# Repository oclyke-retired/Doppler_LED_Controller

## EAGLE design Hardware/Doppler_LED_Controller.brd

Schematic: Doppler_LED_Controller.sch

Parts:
C1, C3, C4, C6, C12, C13, C14, C15, C16, C20: 0.1uF; 0603
C2, C10, C11, C17, C18: 2.2uF; 0603
C5, C9: 10uF; 0603
C7, C8: 18pF; 0603
D1: ESPTX-GREEN; LED-0603
D2: ESP_STAT; APA102_2020_LONG
D3: ESPRX-YELLOW; LED-0603
D4: ULED1-BLUE; LED-0603
D5: ULED2-WHITE; LED-0603
D6: U7TX-GREEN; LED-0603
D8: U7RX-YELLOW; LED-0603
D10: 5.6V; SOD-323
D11: 3A/10V/280mV; SOD-323
D12: PWR-RED; LED-0603
F1: PPTC_6V500MA; 0805
FD1, FD2, FD3, FD4: FIDUCIAL1X2; FIDUCIAL-1X2
H1, H2, H3, H4: STAND-OFF
J1, J2: USB_MICRO-B_HALF_PTH_MILL; USB-MICROB-PTH-MILL
J3: CORTEX_DEBUG_PTH; 2X5-PTH-1.27MM
JP1: ALED1_VOUT_SEL; SMT-JUMPER_3_1-NC_TRACE_SILK
JP2: ALED2_VOUT_SEL; SMT-JUMPER_3_1-NC_TRACE_SILK
JP3: ALED3_VOUT_SEL; SMT-JUMPER_3_1-NC_TRACE_SILK
JP4: ALED4_VOUT_SEL; SMT-JUMPER_3_1-NC_TRACE_SILK
JP5, JP7: I2C1_VOUT_SEL; SMT-JUMPER_3_1-NC_TRACE_SILK
JP6: JUMPER-SMT_2_NO_SILK; SMT-JUMPER_2_NO_SILK
JP9: IMU_VSEL; SMT-JUMPER_3_1-NC_TRACE_SILK
JP10: MPU9250; SMT-JUMPER_2_NO_SILK
JP11: DEFUSE; SMT-JUMPER_2_NO_SILK
M1: EXT_SWTCH; 1X03_SMD_0.1IN
M2: EXT_SWTCH; 3_PIN_LOCK
M3: ALED1_LOCK; 3_PIN_LOCK
M4: ALED2_LOCK; 3_PIN_LOCK
M5: ALED3_LOCK; 3_PIN_LOCK
M6: ALED4_LOCK; 3_PIN_LOCK
M7: ALED1_SMD; 1X03_SMD_0.1IN
M8: ALED2_SMD; 1X03_SMD_0.1IN
M9: ALED3_SMD; 1X03_SMD_0.1IN
M10: ALED4_SMD; 1X03_SMD_0.1IN
M11: I2C1_LOCK; 4_PIN_LOCK
M13: U7_LOCK; 4_PIN_LOCK
M15: I2C1_SMD; 1X04_SMD_0.1IN
M17: U7_SMD; 1X04_SMD_0.1IN
M19: SIG_IN_LOCK; 4_PIN_LOCK
M20: SIG_IN_SMD; 1X04_SMD_0.1IN
M21: SD; SD_AMPHENOL_PUSH_PULL
M22: CONN_SMD_2; 1X02_SMD_0.1IN
M23: CONN_LOCK_2-5055670271; 2_PIN_LOCK
Q1: TRANS_NPN_DUAL-MBT3904DW1T1; SC70-6
Q2, Q3, Q4, Q5, Q6, Q7, Q8, Q9, Q10, Q12, Q14, Q16, Q18, Q19, Q20, Q21: AMP_MOSFET_NCH-2N7002K; SOT23-3
Q22, Q23: 4.3A/20V/54mΩ; SOT23-3
R1, R10: DNP; 0603
R3, R4, R6, R9, R16, R17, R18, R19, R20, R21, R22, R23, R24, R25, R26, R27, R28, R29, R30, R31, R32, R33, R34, R35, R36, R38, R39, R43, R47, R51, R57, R58, R59, R60, R61, R62, R63, R64, R65, R66, R67, R68: 10k; 0603
R7, R8, R11, R12, R53, R55, R69: 1k; 0603
R13, R14: 20; 0603
R37, R41, R45, R49: 2.2k; 0603
S1, S2, S3: US2; TACTILE_SWITCH_SMD_5.2MM
S4: STM_!RST; TACTILE_SWITCH_SMD_5.2MM
S5: US1; TACTILE_SWITCH_SMD_5.2MM
TP1: EDRDY; PAD.03X.04
TP3: ERX0; PAD.03X.04
TP4: ETX0; PAD.03X.04
TP5: E!RTS; PAD.03X.04
TP6: E!DTR; PAD.03X.04
TP7: EMOSI; PAD.03X.04
TP8: EMISO; PAD.03X.04
TP9: ESCLK; PAD.03X.04
TP10: ECS; PAD.03X.04
TP11: ESSI; PAD.03X.04
TP12: ESSCK; PAD.03X.04
TP13: E!RST; PAD.03X.04
TP17: VDDIO; PAD.03X.04
TP18: 1V8; PAD.03X.04
TP20: S1Si; PAD.03X.04
TP21: S1SO; PAD.03X.04
TP22: S1SCLk; PAD.03X.04
TP23: CSSD; PAD.03X.04
TP24: CSIMU; PAD.03X.04
TP25: SDCD; PAD.03X.04
TP29: CSIMUIO; PAD.03X.04
TP30: IMUINT; PAD.03X.04
TP31: IMUFS; PAD.03X.04
TP34: AL1D; PAD.03X.04
TP35: AL2D; PAD.03X.04
TP36: AL3D; PAD.03X.04
TP37: AL4D; PAD.03X.04
TP38: AL1V; PAD.03X.04
TP39: AL2V; PAD.03X.04
TP40: AL3V; PAD.03X.04
TP41: AL4V; PAD.03X.04
TP42: AL1C; PAD.03X.04
TP43: AL2C; PAD.03X.04
TP44: AL3C; PAD.03X.04
TP45: AL4C; PAD.03X.04
TP47: VRPP; PAD.03X.04
TP48: VOVP; PAD.03X.04
TP49: VUSB; PAD.03X.04
TP50: 5V; PAD.03X.04
TP51: 3V3; PAD.03X.04
TP52: GND; PAD.03X.04
TP53: IIC1SDA; PAD.03X.04
TP54: IIC1SCL; PAD.03X.04
TP57: U7TX; PAD.03X.04
TP58: U7RX; PAD.03X.04
TP62: STMR; PAD.03X.04
TP68: SWCLK; PAD.03X.04
TP69: BRK; PAD.03X.04
TP70: LTS; PAD.03X.04
TP71: RTS; PAD.03X.04
TP72: REV; PAD.03X.04
TP78: SWDIO; PAD.03X.04
U1: ESP-WROOM-32
U3: STM32F765VTG6; LQFP-100
U4: 1.8V; DDC5
U5: 9DoF IMU; QFN24-3X3
U6: TXB0108DQSR; UFDFN-20
U7: 3.3V; SOT23-5
U8: CH340C; SO016
U9: W25Q32FVSS; SOIC-8
U$98: REV_NUM
Y1: 24MHz; CRYSTAL-SMD-5X3.2-4PAD

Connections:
1.8V: JP9.3, TP18.P$1, U4.5 (VOUT)
3.3V: C2.1, C3.1, C4.1, C5.1, C6.1, C9.1, C14.1, C16.1, C18.1, C20.1, D1.A, D2.4VCC, D3.A, D4.A, D5.A, D6.A, D8.A, D12.A, J3.1 (VCC), JP1.1, JP2.1, JP3.1, JP4.1, JP5.3, JP6.1, JP7.3, JP9.1, M1.P$2 (2), M2.P$2 (2), M21.CD_SW2, M21.P$4 (VDD), Q2.1 (G), Q3.1 (G), Q4.1 (G), Q5.1 (G), Q6.1 (G), Q7.1 (G), Q8.1 (G), Q9.1 (G), Q10.1 (G), Q12.1 (G), Q14.1 (G), Q16.1 (G), Q18.1 (G), Q19.1 (G), Q20.1 (G), Q21.1 (G), R6.2, R9.2, R17.2, R18.2, R19.2, R21.2, R22.2, R23.2, R24.2, R29.2, R30.2, R31.2, R32.2, R37.2, R39.2, R45.2, R47.2, R57.2, R58.2, R59.2, R60.2, R65.2, R67.2, S3.3 (2), S3.4 (2), S5.3 (2), S5.4 (2), TP51.P$1, U1.2 (3V3), U3.P$6 (6.VBAT), U3.P$11 (11.VDD), U3.P$20 (20.VREF), U3.P$21 (21.VDDA), U3.P$27 (27.VDD), U3.P$50 (50.VDD), U3.P$75 (75.VDD), U3.P$100 (100.VDD), U4.1 (VIN), U4.3 (EN), U5.13 (VDD), U6.16 (VCCB), U7.5 (OUT), U8.4 (V3), U8.16 (VCC), U9.8 (VCC)
5V: C17.1, D11.C, JP1.3, JP2.3, JP3.3, JP4.3, JP5.1, JP7.1, Q23.2 (S), TP50.P$1, U7.1 (IN), U7.3 (EN)
ALED1_MOSI_VOUT: M3.P$1 (1), M7.P$1 (1), Q6.3 (D), R33.1
ALED1_SCLK_VOUT: M3.P$3 (3), M7.P$3 (3), Q2.3 (D), R25.1
ALED1_VOUT: JP1.2, R25.2, R33.2, TP38.P$1
ALED2_MOSI_VOUT: M4.P$1 (1), M8.P$1 (1), Q7.3 (D), R34.1
ALED2_SCLK_VOUT: M4.P$3 (3), M8.P$3 (3), Q3.3 (D), R26.1
ALED2_VOUT: JP2.2, R26.2, R34.2, TP39.P$1
ALED3_MOSI_VOUT: M5.P$1 (1), M9.P$1 (1), Q8.3 (D), R35.1
ALED3_SCLK_VOUT: M5.P$3 (3), M9.P$3 (3), Q4.3 (D), R27.1
ALED3_VOUT: JP3.2, R27.2, R35.2, TP40.P$1
ALED4_MOSI_VOUT: M6.P$1 (1), M10.P$1 (1), Q9.3 (D), R36.1
ALED4_SCLK_VOUT: M6.P$3 (3), M10.P$3 (3), Q5.3 (D), R28.1
ALED4_VOUT: JP4.2, R28.2, R36.2, TP41.P$1
BOOT0: JP6.2, R38.2, U3.P$94 (94.BOOT0)
BRK: Q18.2 (S), R57.1, TP69.P$1, U3.P$81 (81.PD0)
BRK_12V: M19.P$1 (1), M20.P$1 (1), Q18.3 (D), R61.1
CS_ESP: TP10.P$1, U1.29 (CS0_V/IO5), U3.P$4 (4.PE5)
CS_IMU: R67.1, TP24.P$1, U3.P$3 (3.PE4), U6.20 (B1)
CS_IMU_VDDIO: TP29.P$1, U5.22 (!CS), U6.1 (A1)
CS_SD: M21.P$2 (CD/DAT3), R65.1, TP23.P$1, U3.P$2 (2.PE3)
ESP_0: Q1.1 (E), R6.1, S1.1, S1.2 (1), U1.25 (IO0)
ESP_!DTR: Q1.6 (C), R3.2, TP6.P$1, U8.13 (!DTR)
ESP_!RESET: C1.1, Q1.3 (C), R9.1, S2.1, S2.2 (1), TP13.P$1, U1.3 (EN)
ESP_!RTS: Q1.4 (E), R4.2, TP5.P$1, U8.14 (!RTS)
ESP_DRDY: TP1.P$1, U1.24 (IO2), U3.P$9 (9.PC15)
ESP_RXI0: R8.1, TP3.P$1, U1.34 (RXD), U8.2 (TXO)
ESP_STAT_MOSI: D2.1DIN, TP11.P$1, U1.16 (MOSI_H/IO13)
ESP_STAT_SCLK: D2.2CIN, TP12.P$1, U1.13 (SCK_H/IO14)
ESP_TXO0: R7.1, TP4.P$1, U1.35 (TXD), U8.3 (RXI)
ESP_USB_DM: J1.D-, U8.6 (UD-)
ESP_USB_DP: J1.D+, U8.5 (UD+)
GND: C1.2, C2.2, C3.2, C4.2, C5.2, C6.2, C7.1, C8.1, C9.2, C10.2, C11.2, C12.1, C13.2, C14.2, C15.2, C16.2, C17.2, C18.2, C20.2, D2.3GND, D10.A, J1.GND, J2.GND, J3.3 (GND), J3.5 (GND), J3.9 (GNDDTCT), M3.P$2 (2), M4.P$2 (2), M5.P$2 (2), M6.P$2 (2), M7.P$2 (2), M8.P$2 (2), M9.P$2 (2), M10.P$2 (2), M11.P$4 (4), M13.P$4 (4), M15.P$4 (4), M17.P$4 (4), M21.P$6 (VSS1), M22.P$1 (1), M23.P$2 (1), Q22.1 (G), R1.1, R10.1, R16.1, R20.1, R38.1, R61.2, R62.2, R63.2, R64.2, R66.1, R68.1, R69.1, S1.3 (2), S1.4 (2), S2.3 (2), S2.4 (2), S4.3 (2), S4.4 (2), TP52.P$1, U1.1 (GND), U1.15 (GND), U1.38 (GND), U1.GND, U3.P$10 (10.VSS), U3.P$19 (19.VSSA), U3.P$26 (26.VSS), U3.P$49 (49.VSS), U3.P$74 (74.VSS), U3.P$99 (99.VSS), U4.2 (GND), U4.4 (GND), U5.18 (GND), U5.20 (RESV20), U6.15 (GND), U7.2 (GND), U8.1 (GND), U9.4 (GND), Y1.2 (GND), Y1.4 (GND)
I2C1_SCL: Q10.2 (S), R37.1, TP54.P$1, U3.P$95 (95.PB8)
I2C1_SCL_VOUT: M11.P$1 (1), M15.P$1 (1), Q10.3 (D), R41.1
I2C1_SDA: Q14.2 (S), R45.1, TP53.P$1, U3.P$93 (93.PB7)
I2C1_SDA_VOUT: M11.P$2 (2), M15.P$2 (2), Q14.3 (D), R49.1
I2C1_VOUT: JP5.2, M11.P$3 (3), M15.P$3 (3), R41.2, R49.2
I2C2_SCL: U3.P$46 (46.PB10)
I2C2_SDA: U3.P$47 (47.PB11)
IMU_FSYNC: TP31.P$1, U3.P$64 (64.PC7), U6.12 (B7)
IMU_FSYNC_VDDIO: U5.11 (FSYNC), U6.9 (A7)
IMU_INT: TP30.P$1, U3.P$63 (63.PC6), U6.11 (B8)
IMU_INT_VDDIO: U5.12 (INT), U6.10 (A8)
IMU_RESV1: JP10.1, U5.1 (RESV1)
IMU_VDDIO: C13.1, JP9.2, JP10.2, TP17.P$1, U5.8 (VDDIO), U6.5 (VCCA), U6.6 (OE)
LTS: Q19.2 (S), R58.1, TP70.P$1, U3.P$82 (82.PD1)
LTS_12V: M19.P$2 (2), M20.P$2 (2), Q19.3 (D), R62.1
unnamed: J2.SHIELD, J2.SHIELD2 (SHIELD), J2.SHIELD3 (SHIELD), J2.SHIELD4 (SHIELD), J2.SHIELD5 (SHIELD), J2.SHIELD6 (SHIELD), J2.SHIELD7 (SHIELD), J2.SHIELD8 (SHIELD), J2.SHIELD9 (SHIELD), J2.SHIELD10 (SHIELD), R10.2
unnamed: C11.1, U3.P$73 (73.VCAP2)
unnamed: J1.SHIELD, J1.SHIELD2 (SHIELD), J1.SHIELD3 (SHIELD), J1.SHIELD4 (SHIELD), J1.SHIELD5 (SHIELD), J1.SHIELD6 (SHIELD), J1.SHIELD7 (SHIELD), J1.SHIELD8 (SHIELD), J1.SHIELD9 (SHIELD), J1.SHIELD10 (SHIELD), R1.2
unnamed: C10.1, U3.P$48 (48.VCAP1)
unnamed: Q1.5 (B), R3.1
unnamed: Q1.2 (B), R4.1
unnamed: C15.1, U5.10 (REGOUT)
unnamed: D8.C, R55.2
unnamed: J3.2 (SWDIO/TMS), R13.1
unnamed: J3.4 (SWDCLK/TCK), R14.1
unnamed: D6.C, R53.2
unnamed: D1.C, R7.2
unnamed: D3.C, R8.2
unnamed: D12.C, R69.2
unnamed: D5.C, R12.2
unnamed: D4.C, R11.2
PH0: C7.2, U3.P$12 (12.PH0), Y1.3 (2)
PH1: C8.2, U3.P$13 (13.PH1), Y1.1
QSPI_BK1_IO0: Q9.2 (S), R32.1, TP37.P$1, U3.P$58 (58.PD11)
QSPI_BK1_IO1: U3.P$59 (59.PD12)
QSPI_BK1_IO2: U3.P$1 (1.PE2)
QSPI_BK1_IO3: U3.P$60 (60.PD13)
QSPI_BK1_NCS: U3.P$92 (92.PB6)
QSPI_BK2_IO0: U3.P$37 (37.PE7), U9.5 (SI(D0))
QSPI_BK2_IO1: U3.P$38 (38.PE8), U9.2 (SO(D1))
QSPI_BK2_IO2: U3.P$39 (39.PE9), U9.3 (!WP!(D2))
QSPI_BK2_IO3: U3.P$40 (40.PE10), U9.7 (!HOLD!(D3))
QSPI_BK2_NCS: U3.P$79 (79.PC11), U9.1 (!CS!)
QSPI_SCLK: Q5.2 (S), R24.1, TP45.P$1, U3.P$36 (36.PB2), U9.6 (SCK)
REV: Q21.2 (S), R60.1, TP72.P$1, U3.P$84 (84.PD3)
REV_12V: M19.P$4 (4), M20.P$4 (4), Q21.3 (D), R64.1
RTS: Q20.2 (S), R59.1, TP71.P$1, U3.P$83 (83.PD2)
RTS_12V: M19.P$3 (3), M20.P$3 (3), Q20.3 (D), R63.1
SD_CD: M21.CD_SW1, R66.2, TP25.P$1, U3.P$15 (15.PC0)
SPI1_MISO: M21.P$7 (DAT0), TP21.P$1, U3.P$30 (30.PA6), U6.13 (B6)
SPI1_MISO_VDDIO: U5.9 (AD0/SDO), U6.8 (A6)
SPI1_MOSI: M21.P$3 (CMD), TP20.P$1, U3.P$88 (88.PD7), U6.18 (B3)
SPI1_MOSI_VDDIO: U5.24 (SDA/SDI), U6.3 (A3)
SPI1_SCLK: M21.P$5 (CLK), TP22.P$1, U3.P$89 (89.PB3), U6.19 (B2)
SPI1_SCLK_VDDIO: U5.23 (SCL/SCLK), U6.2 (A2)
SPI2_MOSI: Q6.2 (S), R29.1, TP34.P$1, U3.P$16 (16.PC1)
SPI2_SCLK: Q2.2 (S), R21.1, TP42.P$1, U3.P$52 (52.PB13)
SPI3_MOSI: Q7.2 (S), R30.1, TP35.P$1, U3.P$87 (87.PD6)
SPI3_SCLK: Q3.2 (S), R22.1, TP43.P$1, U3.P$78 (78.PC10)
SPI4_MOSI: Q8.2 (S), R31.1, TP36.P$1, U3.P$5 (5.PE6)
SPI4_SCLK: Q4.2 (S), R23.1, TP44.P$1, U3.P$42 (42.PE12)
SPI6_MISO: TP8.P$1, U1.31 (MISO_V/IO19), U3.P$90 (90.PB4)
SPI6_MOSI: TP7.P$1, U1.37 (MOSI_V/IO23), U3.P$31 (31.PA7)
SPI6_SCLK: TP9.P$1, U1.30 (SCK_V/IO18), U3.P$29 (29.PA5)
STM_!RESET: C12.2, J3.10 (!RESET), R19.1, S4.1, S4.2 (1), TP62.P$1, U3.P$14 (14.NRST)
STM_USB_DM: J2.D-, U3.P$70 (70.PA11)
STM_USB_DP: J2.D+, U3.P$71 (71.PA12)
SWCLK: R14.2, R17.1, TP68.P$1, U3.P$76 (76.PA14)
SWDIO: R13.2, R18.1, TP78.P$1, U3.P$72 (72.PA13)
UART4_RX: U1.28 (IO17), U3.P$23 (23.PA1)
UART4_TX: U1.27 (IO16), U3.P$22 (22.PA0)
UART5_RX: U3.P$51 (51.PB12)
UART5_TX: U3.P$80 (80.PC12)
UART8_RX: U3.P$97 (97.PE0)
UART8_TX: U3.P$98 (98.PE1)
ULED1: R11.1, U3.P$7 (7.PC13)
ULED2: R12.1, U3.P$8 (8.PC14)
US1: M1.P$3 (3), M2.P$3 (3), R20.2, S5.1, S5.2 (1), U3.P$85 (85.PD4)
US2: M1.P$1 (1), M2.P$1 (1), R16.2, S3.1, S3.2 (1), U3.P$86 (86.PD5)
USART1_RX: Q16.2 (S), R47.1, R55.1, TP58.P$1, U3.P$54 (54.PB15)
USART1_RX_VOUT: M13.P$1 (1), M17.P$1 (1), Q16.3 (D), R51.1
USART1_TX: Q12.2 (S), R39.1, R53.1, TP57.P$1, U3.P$53 (53.PB14)
USART1_TX_VOUT: M13.P$2 (2), M17.P$2 (2), Q12.3 (D), R43.1
USART1_VOUT: JP7.2, M13.P$3 (3), M17.P$3 (3), R43.2, R51.2
USB_OTG_FS_ID: J2.ID, U3.P$69 (69.PA10)
USB_OTG_FS_SOF: U3.P$67 (67.PA8)
VOVP: D10.C, F1.2, JP11.2, Q23.3 (D), TP48.P$1
VRAW: M22.P$2 (2), M23.P$3 (2), Q22.3 (D)
VRPP: F1.1, JP11.1, Q22.2 (S), TP47.P$1
V_USB: D11.A, J1.VBUS, J2.VBUS, Q23.1 (G), R68.2, TP49.P$1, U3.P$68 (68.PA9)

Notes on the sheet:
Completed peripherals
SPI1
SPI2 (TX only)
SPI3 (TX only)
SPI4 (TX only)
QSPI (BK1)
SPI6
UART4
UART5
UART7
UART8
I2C1
I2C2
Connect jumper if using MPU9250
ICM 20948 : 1.8V MPU 9250 : 3.3V
Max input: 6V
STM32
ESP32
SPI1 Devices
Power Supply
Output Conditioning
Input Conditioning

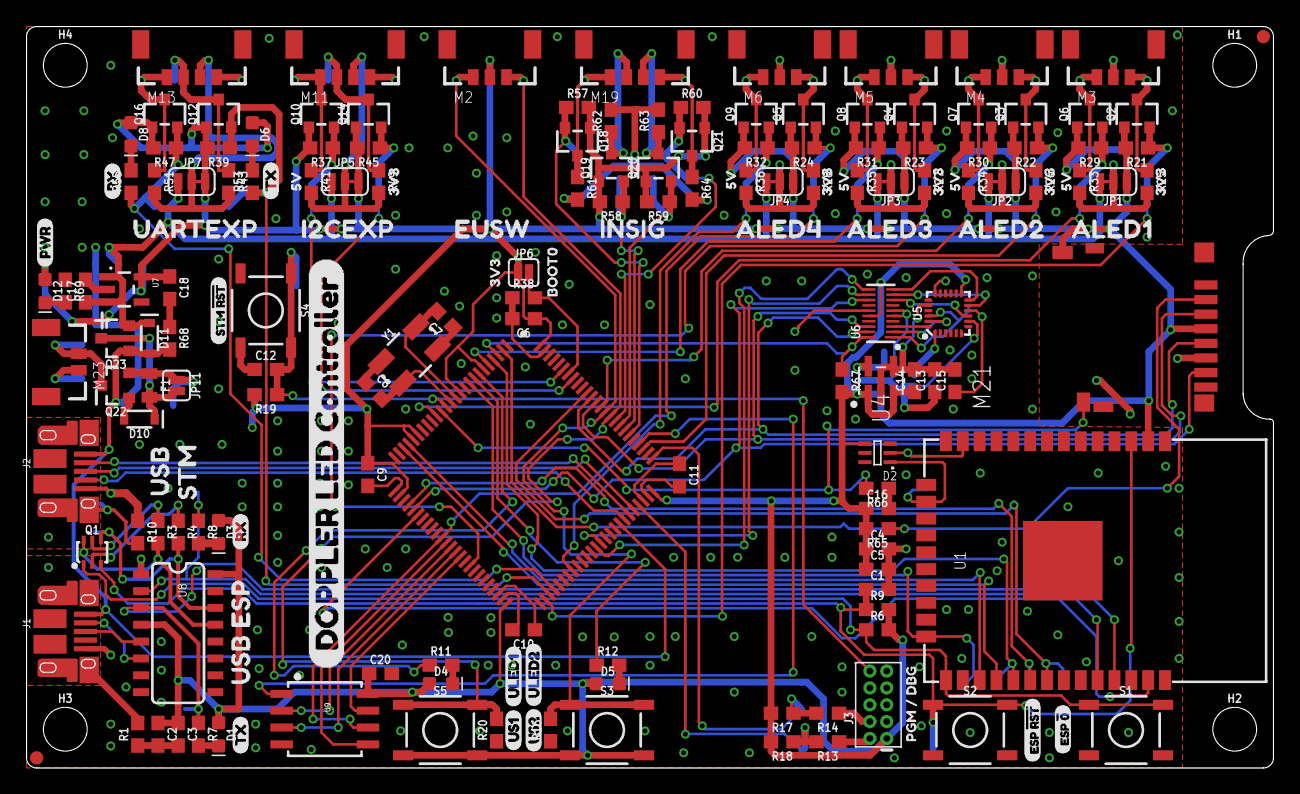
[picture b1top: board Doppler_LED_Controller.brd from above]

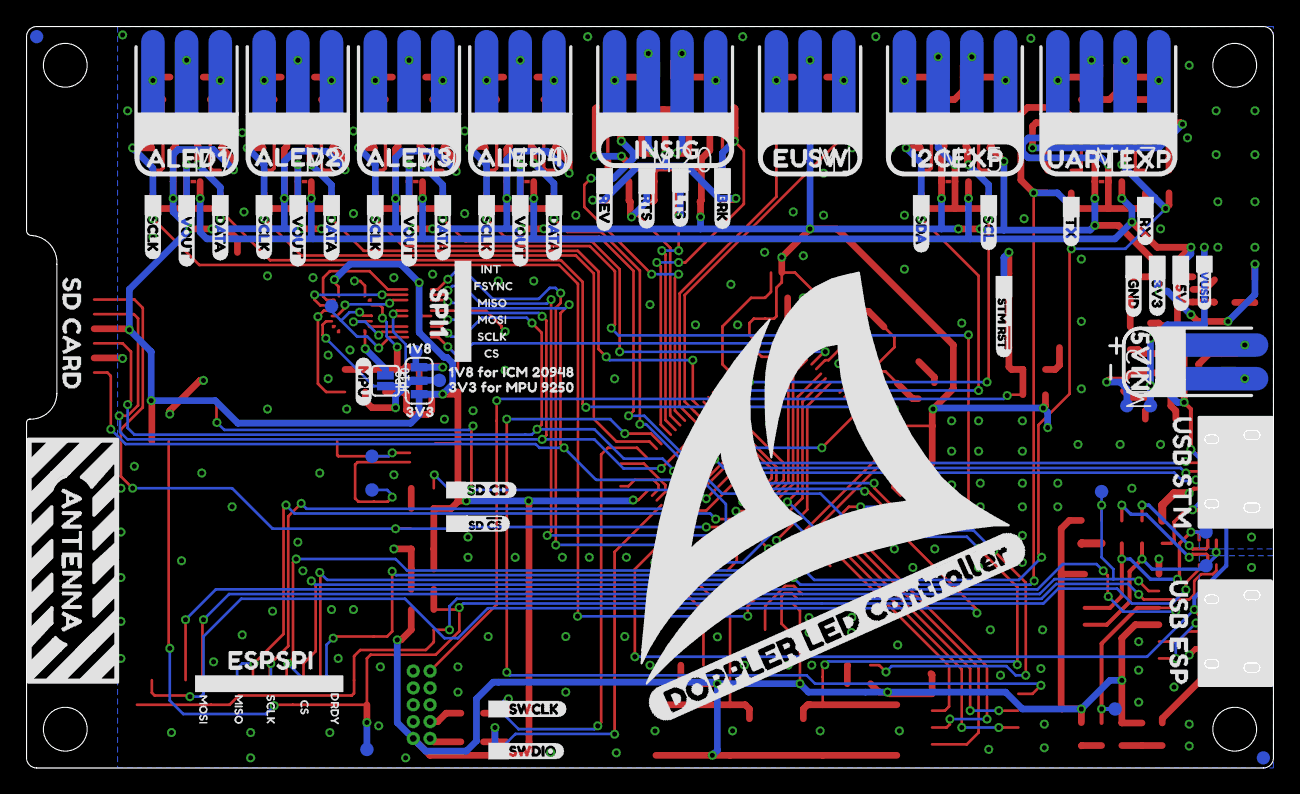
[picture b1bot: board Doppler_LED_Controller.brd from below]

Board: 2 copper layers, 94.0 x 55.9 mm, 311 parts (127 on the bottom side), 113 nets.

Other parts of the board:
U$1, U$74: ALED10
U$2, U$75: ALED21
U$3: ALED43
U$4, U$76: ALED33
U$5, U$78: INSIG4
U$6, U$79: UARTEXP7
U$7, U$80: I2CEXP6
U$8, U$81: EUSW5
U$9, U$10, U$11, U$12: SCLK1
U$13, U$14, U$15, U$16: VOUT2
U$17, U$18, U$19, U$20: DATA0
U$21: RTS4
U$22: LTS3
U$23: BRK5
U$24: REV6
U$25: SCL8
U$26: SDA7
U$27, U$63, U$66: TX9
U$28, U$64, U$67: RX10
U$29: 5VIN8
U$30: VUSB15
U$31: 5V14
U$32: 3V313
U$33: GND12
U$34: SWCLK16
U$35: SWDIO15
U$36, U$48: SCLK20
U$37, U$49: CS21
U$38, U$47: MISO18
U$39, U$46: MOSI17
U$40: DRDY19
U$41: ESPSPI9
U$42: ANTENNA10
U$43: SD_CARD11
U$44, U$71: USB_ESP12
U$45: USB_STM13
U$50: FSYNC23
U$51: INT22
U$52: STM_#RST26
U$53: SD_#CS24
U$54: SD_CD27
U$55, U$68: DOPPLER_LED_CONTROLLER0
U$56: ULED23
U$57: ULED12
U$58: US10
U$59: US21
U$60: ESP_#RST5
U$61: ESP_#06
U$62: PGM_#_DBG7
U$65: PWR8
U$69: STM_#RST24
U$72, U$82, U$83, U$84, U$85, U$86: 3V310
U$73: BOOT09
U$77: ALED42
U$87, U$88, U$89, U$90, U$91: 5V11
U$92: SPI116
U$93: 3V39
U$94: 1V817
U$95: 1V8_FOR_ICM_2094818
U$96: 3V3_FOR_MPU_925019
U$97: MPU20
U$99: USB0
U$100: STM1

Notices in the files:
parts and their libraries:
SparkFun-Capacitors: Licensing: Creative Commons ShareAlike 4.0 International - https://creativecommons.org/licenses/by-sa/4.0
SparkFun-DigitalIC: Licensing: CC v3.0 Share-Alike You are welcome to use this library for commercial purposes.
MTAES_V2_UniqueParts: Released under the Creative Commons
